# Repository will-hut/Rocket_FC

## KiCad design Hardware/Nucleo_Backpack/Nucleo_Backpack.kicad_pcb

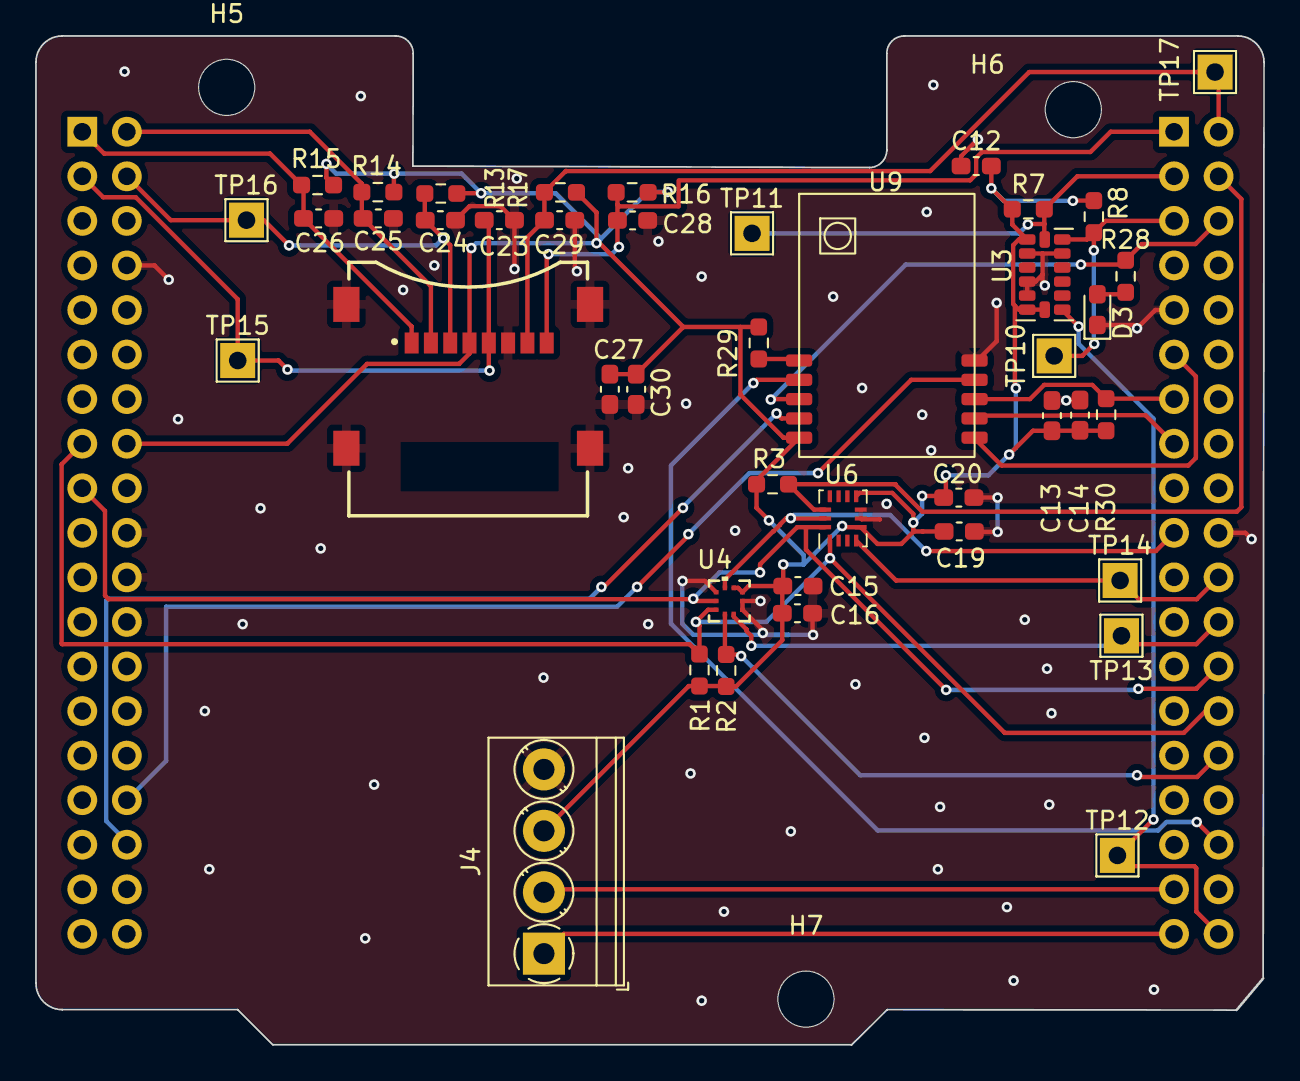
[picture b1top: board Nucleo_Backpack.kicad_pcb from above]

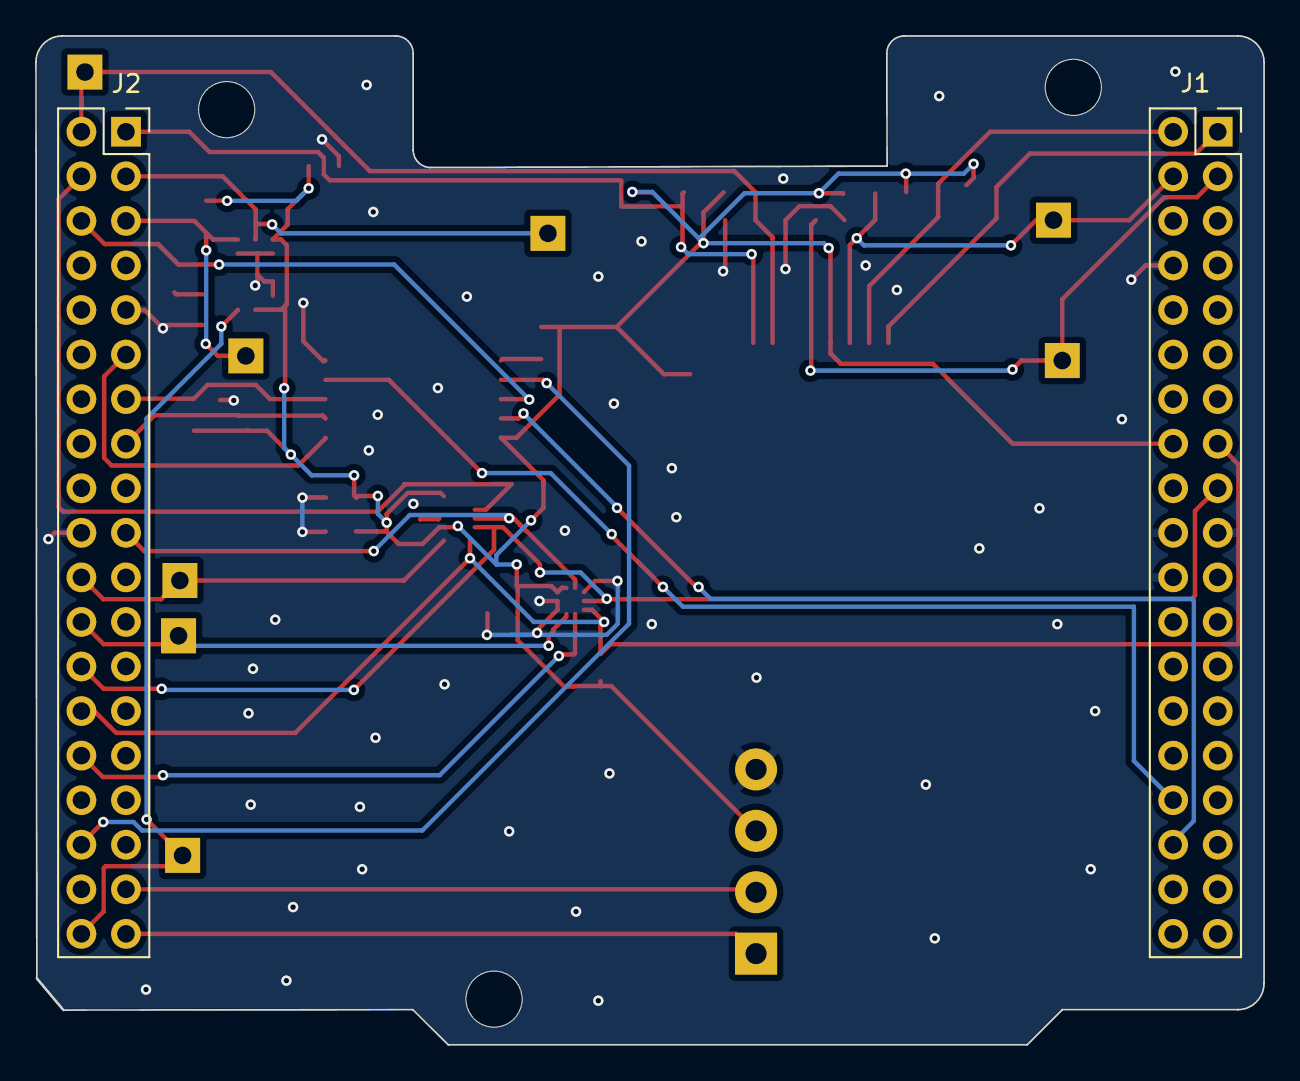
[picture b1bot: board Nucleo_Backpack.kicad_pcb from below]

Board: 2 copper layers, 70.0 x 57.5 mm, 48 parts (2 on the bottom side), 29 nets.

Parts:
C12, C13, C15, C16, C19, C20, C30: 100n; C_0603_1608Metric_Pad1.08x0.95mm_HandSolder
C14, C27: 10u; C_0603_1608Metric_Pad1.08x0.95mm_HandSolder
C23, C24, C25, C26, C28, C29: 22p; C_0603_1608Metric_Pad1.08x0.95mm_HandSolder
D3: BUSY; LED_0603_1608Metric_Pad1.05x0.95mm_HandSolder
H5, H6, H7: MountingHole; MountingHole_3.2mm_M3
J1: CN7; PinSocket_2x19_P2.54mm_Vertical
J2: CN10; PinSocket_2x19_P2.54mm_Vertical
J4: Conn_01x04; TerminalBlock_Phoenix_PT-1,5-4-3.5-H_1x04_P3.50mm_Horizontal
J5: MEM2067-02-180-00-A_REVB; GCT_MEM2067-02-180-00-A_REVB
R1, R2, R3, R28, R30: 22k; R_0603_1608Metric_Pad0.98x0.95mm_HandSolder
R7, R8: 4.7k; R_0603_1608Metric_Pad0.98x0.95mm_HandSolder
R13, R14, R15, R16, R17, R29: 10k; R_0603_1608Metric_Pad0.98x0.95mm_HandSolder
TP10: SDA; TestPoint_THTPad_2.0x2.0mm_Drill1.0mm
TP11: SCL; TestPoint_THTPad_2.0x2.0mm_Drill1.0mm
TP12: ACC_INT; TestPoint_THTPad_2.0x2.0mm_Drill1.0mm
TP13: BARO_INT; TestPoint_THTPad_2.0x2.0mm_Drill1.0mm
TP14: IMU_INT; TestPoint_THTPad_2.0x2.0mm_Drill1.0mm
TP15: SD_CLK; TestPoint_THTPad_2.0x2.0mm_Drill1.0mm
TP16: SD_CMD; TestPoint_THTPad_2.0x2.0mm_Drill1.0mm
TP17: SD_D0; TestPoint_THTPad_2.0x2.0mm_Drill1.0mm
U3: ADXL375; LGA-14_3x5mm_P0.8mm_LayoutBorder1x6y
U4: BMP390; LGA10_BMP390_BOS
U6: BMI323; Bosch_LGA-14_3x2.5mm_P0.5mm
U9: LR62E

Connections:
+3.3V: C12.2, C13.1, C14.1, C15.1, C16.1, C19.1, C20.1, C27.1, C30.1, J1.16, J4.3, J5.4 (VDD), R1.1, R2.1, R3.1, R7.1, R8.1, R13.1, R14.1, R15.1, R16.1, R17.1, R29.1, R30.1, U3.1 (VDDIO), U3.6 (VS), U3.7 (~CS), U4.1 (VDDIO), U4.10 (VDD), U6.5 (VDDIO), U6.8 (VDD), U9.5 (VDD)
ACCEL_INT: J2.38, TP12.1, U3.8 (INT1)
BARO_INT: J2.24, TP13.1, U4.7 (INT)
GND: C12.1, C13.2, C14.2, C15.2, C16.2, C19.2, C20.2, C23.2, C24.2, C25.2, C26.2, C27.2, C28.2, C29.2, C30.2, D3.1 (K), J1.8, J1.19, J1.20, J1.22, J2.9, J2.20, J4.4, J5.6 (VSS), J5.9 (SHIELD), J5.10 (SHIELD), J5.11 (SHIELD), J5.12 (SHIELD), U3.2 (GND), U3.4 (GND), U3.5 (GND), U3.12 (SDO/ADDR), U4.3 (VSS), U4.8 (VSS), U4.9 (VSS), U6.6 (GNDIO), U6.7 (GND), U9.10 (GND)
I2C1_SCL: J2.3, R7.2, TP11.1, U3.14 (SCK)
I2C1_SDA: J2.5, R8.2, TP10.1, U3.13 (SDI/SDA)
IMU_INT: J2.22, TP14.1, U6.4 (INT1)
unnamed: D3.2 (A), R28.2
unnamed: R29.2, U9.1 (ANT_SW)
RADIO_BUSY: J2.6, R28.1, U9.3 (BUSY)
RADIO_DIO1: J1.34, U9.4 (DIO1)
RADIO_RST: J2.34, U9.2 (NRST)
SDIO_CK: C23.1, J1.3, J5.5 (CLK), TP15.1
SDIO_CMD: C24.1, J1.4, J5.3 (CMD), R13.2, TP16.1
SDIO_D0: C29.1, J2.2, J5.7 (DAT0), R17.2, TP17.1
SDIO_D1: C28.1, J2.1, J5.8 (DAT1), R16.2
SDIO_D2: C26.1, J1.1, J5.1 (DAT2), R15.2
SDIO_D3: C25.1, J1.2, J5.2 (CD/DAT3), R14.2
SPI1_MISO: J2.13, R30.2, U9.8 (MISO)
SPI1_MOSI: J2.15, U9.7 (MOSI)
SPI1_NSS: J1.32, U9.9 (NSS)
SPI1_SCK: J2.11, U9.6 (SCK)
SPI2_CS1: J2.30, R2.2, U4.6 (CSB)
SPI2_CS2: J2.4, R3.2, U6.12 (CSB)
SPI2_MISO: J1.15, J2.28, R1.2, U4.5 (SDO), U6.1 (SDO)
SPI2_MOSI: J1.17, J2.26, U4.4 (SDI), U6.14 (SDI)
SPI2_SCK: J2.19, U4.2 (SCK), U6.13 (SCK)
USART2_RX: J2.37, J4.1
USART2_TX: J2.35, J4.2

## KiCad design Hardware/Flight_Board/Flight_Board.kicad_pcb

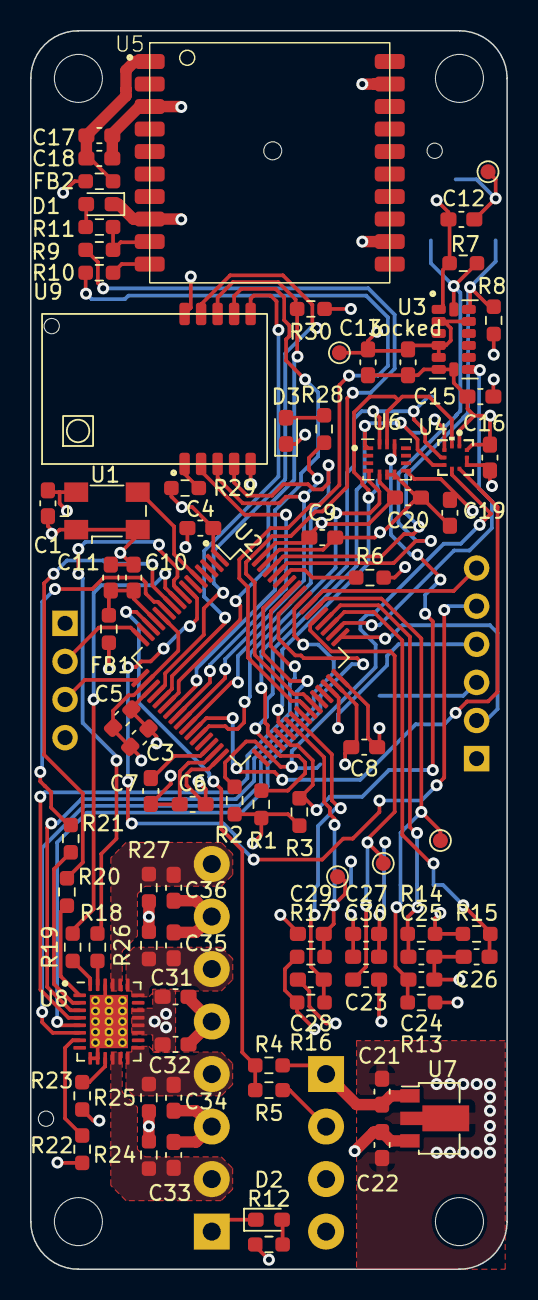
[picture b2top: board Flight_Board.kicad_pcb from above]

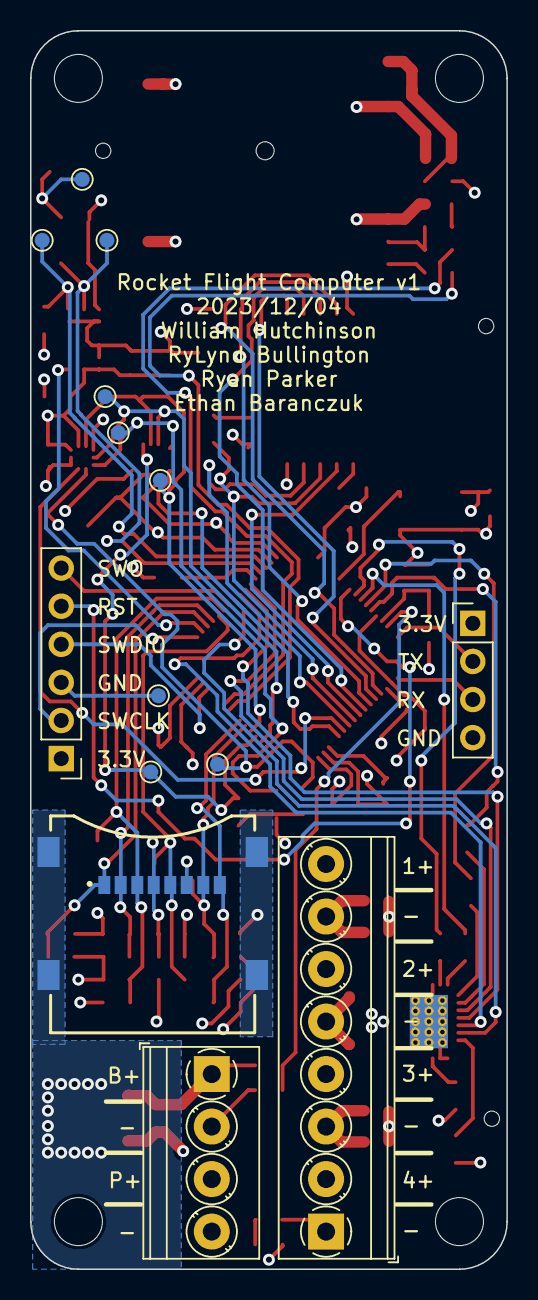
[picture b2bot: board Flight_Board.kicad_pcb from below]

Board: 4 copper layers, 31.8 x 82.6 mm, 105 parts (14 on the bottom side), 65 nets.

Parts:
C1, C4, C5, C6, C8, C9, C10, C12, C13, C15, C16, C18, C19, C20, C30, C32: 100n; C_0603_1608Metric_Pad1.08x0.95mm_HandSolder
C3, C27: 10u; C_0603_1608Metric_Pad1.08x0.95mm_HandSolder
C7: 4.7u LOWESR; C_0603_1608Metric_Pad1.08x0.95mm_HandSolder
C11, C17, C21: 1u; C_0603_1608Metric_Pad1.08x0.95mm_HandSolder
C22: 2.2u; C_0603_1608Metric_Pad1.08x0.95mm_HandSolder
C23, C24, C25, C26, C28, C29: 22p; C_0603_1608Metric_Pad1.08x0.95mm_HandSolder
C31: 10n; C_0603_1608Metric_Pad1.08x0.95mm_HandSolder
C33, C34, C35, C36: 22n; C_0603_1608Metric_Pad1.08x0.95mm_HandSolder
D1: GPS_TX; LED_0603_1608Metric_Pad1.05x0.95mm_HandSolder
D2: POWER; LED_0603_1608Metric_Pad1.05x0.95mm_HandSolder
D3: BUSY; LED_0603_1608Metric_Pad1.05x0.95mm_HandSolder
FB1, FB2: FerriteBead; R_0603_1608Metric_Pad0.98x0.95mm_HandSolder
H1, H2, H3, H4: MountingHole; MountingHole_3.2mm_M3_ISO14580
H5, H6, H7: MountingHole; Stencil_hole
J1: Conn_01x04; TerminalBlock_Phoenix_PT-1,5-4-3.5-H_1x04_P3.50mm_Horizontal
J2: Conn_01x08; TerminalBlock_Phoenix_PT-1,5-8-3.5-H_1x08_P3.50mm_Horizontal
J3: Conn_01x04; PinHeader_1x04_P2.54mm_Vertical
J4: Conn_01x06; PinHeader_1x06_P2.54mm_Vertical
J5: MEM2067-02-180-00-A_REVB; GCT_MEM2067-02-180-00-A_REVB
R1, R2, R3, R4, R11, R12, R24, R25, R26, R27, R28, R30: 22k; R_0603_1608Metric_Pad0.98x0.95mm_HandSolder
R5, R6, R13, R14, R15, R16, R17, R23, R29: 10k; R_0603_1608Metric_Pad0.98x0.95mm_HandSolder
R7, R8, R18, R19, R20, R21: 4.7k; R_0603_1608Metric_Pad0.98x0.95mm_HandSolder
R9, R10: 220; R_0603_1608Metric_Pad0.98x0.95mm_HandSolder
R22: 1k; R_0603_1608Metric_Pad0.98x0.95mm_HandSolder
TP1, TP2, TP3, TP4: GND; TestPoint_Pad_D1.0mm
TP5: MISO; TestPoint_Pad_D1.0mm
TP6: MOSI; TestPoint_Pad_D1.0mm
TP7: SCK; TestPoint_Pad_D1.0mm
TP8: CS1; TestPoint_Pad_D1.0mm
TP9: CS2; TestPoint_Pad_D1.0mm
TP10: SDA; TestPoint_Pad_D1.0mm
TP11: SCL; TestPoint_Pad_D1.0mm
TP15: SD_CLK; TestPoint_Pad_D1.0mm
TP16: SD_CMD; TestPoint_Pad_D1.0mm
TP17: SD_D0; TestPoint_Pad_D1.0mm
U1: FT5HN; Oscillator_SMD_Fox_FT5H_5.0x3.2mm
U2: STM32F411RCTx; LQFP-64_10x10mm_P0.5mm
U3: ADXL375; LGA-14_3x5mm_P0.8mm_LayoutBorder1x6y
U4: BMP390; LGA10_BMP390_BOS
U5: FGPMMOPA6H
U6: BMI323; Bosch_LGA-14_3x2.5mm_P0.5mm
U7: AP2205-33Y-13; SOT-89-3
U8: TPS274160A
U9: LR62E
locked: 10u; C_0603_1608Metric_Pad1.08x0.95mm_HandSolder

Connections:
+3.3V: C1.1, C3.1, C4.1, C5.1, C6.1, C8.1, C9.1, C12.2, C13.1, C15.1, C16.1, C19.1, C20.1, C22.1, C27.1, C30.1, FB1.1, FB2.1, J3.1, J4.1, J5.4 (VDD), R1.1, R2.1, R3.1, R7.1, R8.1, R12.1, R13.1, R14.1, R15.1, R16.1, R17.1, R23.1, R29.1, R30.1, U1.4 (VDD), U2.1 (VBAT), U2.19 (VDD), U2.32 (VDD), U2.48 (VDD), U2.64 (VDD), U3.1 (VDDIO), U3.6 (VS), U3.7 (~CS), U4.1 (VDDIO), U4.10 (VDD), U6.5 (VDDIO), U6.8 (VDD), U7.3 (VOUT), U9.5 (VDD), locked.1
/Accelerometer/INT1: U2.50 (PA15), U3.8 (INT1)
/Accelerometer/SCL: R7.2, TP11.1, U2.61 (PB8), U3.14 (SCK)
/Accelerometer/SDA: R8.2, TP10.1, U2.62 (PB9), U3.13 (SDI/SDA)
/Barometer/INT: U2.27 (PB1), U4.7 (INT)
/Barometer/MISO: R1.2, TP5.1, U2.35 (PB14), U4.5 (SDO), U6.1 (SDO)
/Barometer/MOSI: TP6.1, U2.36 (PB15), U4.4 (SDI), U6.14 (SDI)
/Barometer/SCK: TP7.1, U2.38 (PC7), U4.2 (SCK), U6.13 (SCK)
/CS1: R2.2, TP8.1, U2.34 (PB13), U4.6 (CSB)
/CS2: R3.2, TP9.1, U2.37 (PC6), U6.12 (CSB)
/Current Switch/EN1: R18.1, U2.8 (PC0)
/Current Switch/EN2: R19.1, U2.9 (PC1)
/Current Switch/EN3: R20.1, U2.10 (PC2)
/Current Switch/EN4: R21.1, U2.11 (PC3)
/Current Switch/~ST1: U2.59 (PB7), U8.3 (~ST1)
/Current Switch/~ST2: U2.58 (PB6), U8.4 (~ST2)
/Current Switch/~ST3: U2.57 (PB5), U8.5 (~ST3)
/Current Switch/~ST4: U2.56 (PB4), U8.6 (~ST4)
/GPS/RXD: R10.1, U2.42 (PA9)
/GPS/TXD: R9.2, U2.43 (PA10)
/IMU/INT1: U2.28 (PB2), U6.4 (INT1)
/LoRa/LORA_BUSY: R28.1, U2.25 (PC5), U9.3 (BUSY)
/LoRa/LORA_DIO1: U2.26 (PB0), U9.4 (DIO1)
/LoRa/LORA_MISO: R30.2, U2.22 (PA6), U9.8 (MISO)
/LoRa/LORA_MOSI: U2.23 (PA7), U9.7 (MOSI)
/LoRa/LORA_NSS: U2.20 (PA4), U9.9 (NSS)
/LoRa/LORA_RST: U2.24 (PC4), U9.2 (NRST)
/LoRa/LORA_SCK: U2.21 (PA5), U9.6 (SCK)
/MicroSD/SDIO_CLK: C23.1, J5.5 (CLK), TP15.1, U2.53 (PC12)
/MicroSD/SDIO_CMD: C24.1, J5.3 (CMD), R13.2, TP16.1, U2.54 (PD2)
/MicroSD/SDIO_D0: C29.1, J5.7 (DAT0), R17.2, TP17.1, U2.39 (PC8)
/MicroSD/SDIO_D1: C28.1, J5.8 (DAT1), R16.2, U2.40 (PC9)
/MicroSD/SDIO_D2: C26.1, J5.1 (DAT2), R15.2, U2.51 (PC10)
/MicroSD/SDIO_D3: C25.1, J5.2 (CD/DAT3), R14.2, U2.52 (PC11)
/Microcontroller/NRST: J4.5, U2.7 (NRST)
/Microcontroller/SWCLK: J4.2, U2.49 (PA14)
/Microcontroller/SWDIO: J4.4, U2.46 (PA13)
/Microcontroller/SWO: J4.6, U2.55 (PB3)
/Microcontroller/TCXO_OUT: U1.3 (OUT), U2.5 (PH0)
/Microcontroller/UART_RX: J3.3, U2.17 (PA3)
/Microcontroller/UART_TX: J3.2, U2.16 (PA2)
/Microcontroller/VBAT_ADC: R4.2, R5.1, U2.14 (PA0)
/PYRO1: C36.1, J2.8, R27.2, U8.24 (OUT1), U8.25 (OUT1)
/PYRO2: C35.1, J2.6, R26.2, U8.22 (OUT2), U8.23 (OUT2)
/PYRO3: C34.1, J2.4, R25.2, U8.14 (OUT3), U8.15 (OUT3)
/PYRO4: C33.1, J2.2, R24.2, U8.12 (OUT4), U8.13 (OUT4)
/VBAT: C21.1, J1.1, R4.1, U7.1 (VIN)
/VPYRO: C31.1, C32.1, J1.3, R24.1, R25.1, R26.1, R27.1, U8.17 (VS), U8.18 (VS), U8.19 (VS), U8.20 (VS)
GND: C1.2, C3.2, C4.2, C5.2, C6.2, C7.2, C8.2, C9.2, C10.2, C11.2, C12.1, C13.2, C15.2, C16.2, C17.2, C18.2, C19.2, C20.2, C21.2, C22.2, C23.2, C24.2, C25.2, C26.2, C27.2, C28.2, C29.2, C30.2, C31.2, C32.2, C33.2, C34.2, C35.2, C36.2, D1.1 (K), D2.1 (K), D3.1 (K), J1.2, J1.4, J2.1, J2.3, J2.5, J2.7, J3.4, J4.3, J5.6 (VSS), J5.9 (SHIELD), J5.10 (SHIELD), J5.11 (SHIELD), J5.12 (SHIELD), R5.2, R6.2, R22.1, TP1.1, TP2.1, TP3.1, TP4.1, U1.1 (GND), U1.2 (GND), U2.12 (VSSA), U2.18 (VSS), U2.31 (VSS), U2.47 (VSS), U2.63 (VSS), U3.2 (GND), U3.4 (GND), U3.5 (GND), U3.12 (SDO/ADDR), U4.3 (VSS), U4.8 (VSS), U4.9 (VSS), U5.3 (GND), U5.8 (GND), U5.12 (GND), U5.19 (GND), U6.6 (GNDIO), U6.7 (GND), U7.2 (GND), U8.9 (GND), U8.10 (THER), U8.26 (GND), U8.29 (PAD), U9.10 (GND), locked.2
unnamed: D1.2 (A), R11.2
unnamed: D2.2 (A), R12.2
unnamed: D3.2 (A), R28.2
unnamed: R6.1, U2.60 (BOOT0)
unnamed: C7.1, U2.30 (VCAP1)
unnamed: C10.1, C11.1, FB1.2, U2.13 (VDDA)
unnamed: R10.2, U5.10 (RX)
unnamed: R9.1, R11.1, U5.9 (TX)
unnamed: C17.1, C18.1, FB2.2, U5.1 (VCC)
unnamed: R22.2, U8.7 (CL)
unnamed: R23.2, U8.11 (DIAG_EN)
unnamed: R18.2, U8.27 (EN1)
unnamed: R19.2, U8.28 (EN2)
unnamed: R20.2, U8.1 (EN3)
unnamed: R21.2, U8.2 (EN4)
unnamed: R29.2, U9.1 (ANT_SW)

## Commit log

2023-10-24 add initial hardware symbols/footprints
2023-10-26 add main microcontroller schematic
2023-10-26 Added Pages to Schematic Hierarchy
    Added GPS, Barometer, Accelerometer, and IMU pages. Also included parts on all pages to start schematic design.
2023-10-26 Remove lock file
    did cool stuff
2023-10-26 Added initial design for Accel.
    Created initial schematics for accelerometer and VS headers on Page 2
2023-10-26 Make Barometer
2023-10-26 Fix Barometer SDO Pin Direction
2023-10-26 standardize connections and create initial spi2 bus
2023-10-26 Make GPS
2023-10-26 move ADLX375 to I2C, bring out more mcu pins, and general touchups
2023-10-26 Added Power Page
    Power page added
2023-10-26 fix rx/tx lines
2023-10-27 add MicroSD
2023-10-27 make Current Switch
2023-10-27 remove STBar pullups
    note made to toggle internal pullups on mcu to handle external pullups for diagnostic lines
2023-10-27 fix gitignore for mac
2023-10-27 Added LoRa board sheet and basic component
2023-10-27 Updated Lora Board
2023-10-27 Update LoRa 2
2023-10-27 fix current limiter
    reverse polarity protection diode&res removed
    split/fix caps on current switch VDD
2023-10-27 connect 4th output channel
2023-10-27 Created power schematic
2023-10-28 clean up and finalize initial design
2023-11-01 Added Mason's Feedback
2023-11-01 Clean up, relabel all refdes, and add autosaved files to gitignore
2023-11-03 clean up, implement suggestions from saunders
2023-11-03 update revision number to v2
2023-11-10 Add LEDs and test points
2023-11-10 final touches, bom, footprints
2023-11-13 fix some stuff and begin layout grouping
2023-11-16 Majority of routing attempted
    I got carried away with a lot of random stuff
2023-11-16 route buck and current switch
2023-11-17 initial placement on board, continue routing
2023-11-17 flip mcu pins around, improve routability
2023-11-17 Second attempt
    Routing complete, check it out
2023-11-17 add ground plane and begin stitching
2023-11-18 stitch ground plane
2023-11-18 fix remaining drc errors
    hole sizes for current switch increased
2023-11-20 add new gps
2023-11-20 begin 4 layer board
2023-11-20 begin fixing silkscreen
2023-11-20 change current switch footprint
2023-11-20 edit pcb with new footprint
2023-11-20 update current switch from main branch
2023-11-22 initial route of 4-layer board
    ouch
2023-11-22 silkscreen cleanup
2023-11-27 update silkscreen
2023-11-27 fix track stub and generate first gerbers
2023-12-01 reroute inner traces and tx/rx GPS lines
2023-12-01 reroute floating traces in radio void
2023-12-01 create backpack board project and fix sikscreen
2023-12-01 Made Beginning breakout for Nucleo Backpack
2023-12-01 Added Components to PCB for Backpack
2023-12-01 all components now on the backpack
2023-12-02 Backpack done except grounding
2023-12-02 Updated backpack
    Changed track width to 0.3mm
2023-12-04 minor tweaks and prettification
2023-12-04 add stencil holes
2023-12-04 Backpack Updates
2023-12-04 Backpack Update
2023-12-05 cleaned up boards
2023-12-05 regenerate gerbers
